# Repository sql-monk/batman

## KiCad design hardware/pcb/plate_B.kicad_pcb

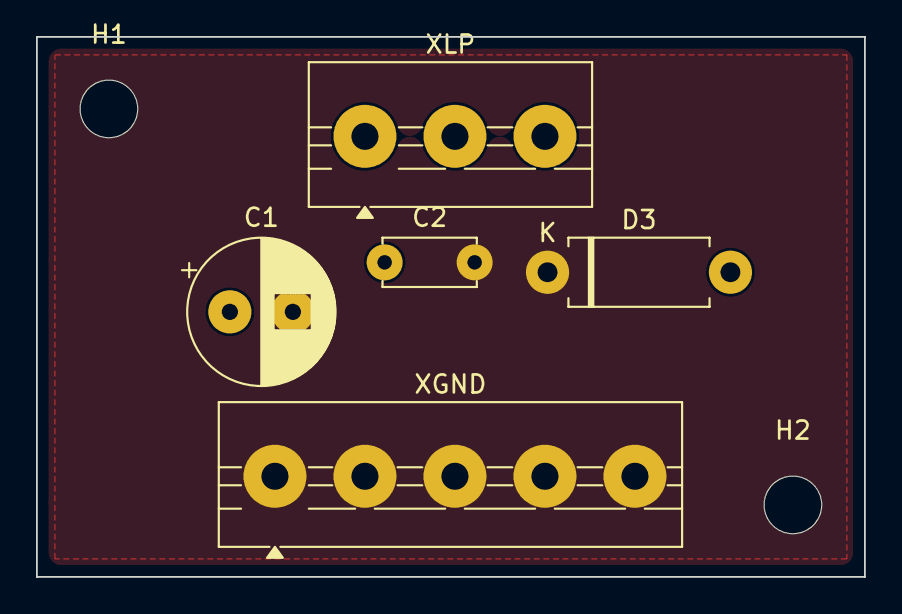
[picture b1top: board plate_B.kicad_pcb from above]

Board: 2 copper layers, 46.0 x 30.0 mm, 7 parts (0 on the bottom side), 2 nets, no tracks yet.

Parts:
C1: 100µ 50V; CP_Radial_D8.0mm_P3.50mm
C2: 100n; C_Disc_D5.0mm_W2.5mm_P5.00mm
D3: SMBJ33A / 1.5KE33; D_DO-15_P10.16mm_Horizontal
H1, H2: MountingHole_3.2mm_M3
XGND: GND-шина (P24–P28); TerminalBlock_MaiXu_MX126-5.0-05P_1x05_P5.00mm
XLP: LOAD+ (P06 P12 P13); TerminalBlock_MaiXu_MX126-5.0-03P_1x03_P5.00mm

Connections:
GND: C1.2, C2.2, D3.1, XGND.1, XGND.2, XGND.3, XGND.4, XGND.5
LOAD+: C1.1, C2.1, D3.2, XLP.1, XLP.2, XLP.3
